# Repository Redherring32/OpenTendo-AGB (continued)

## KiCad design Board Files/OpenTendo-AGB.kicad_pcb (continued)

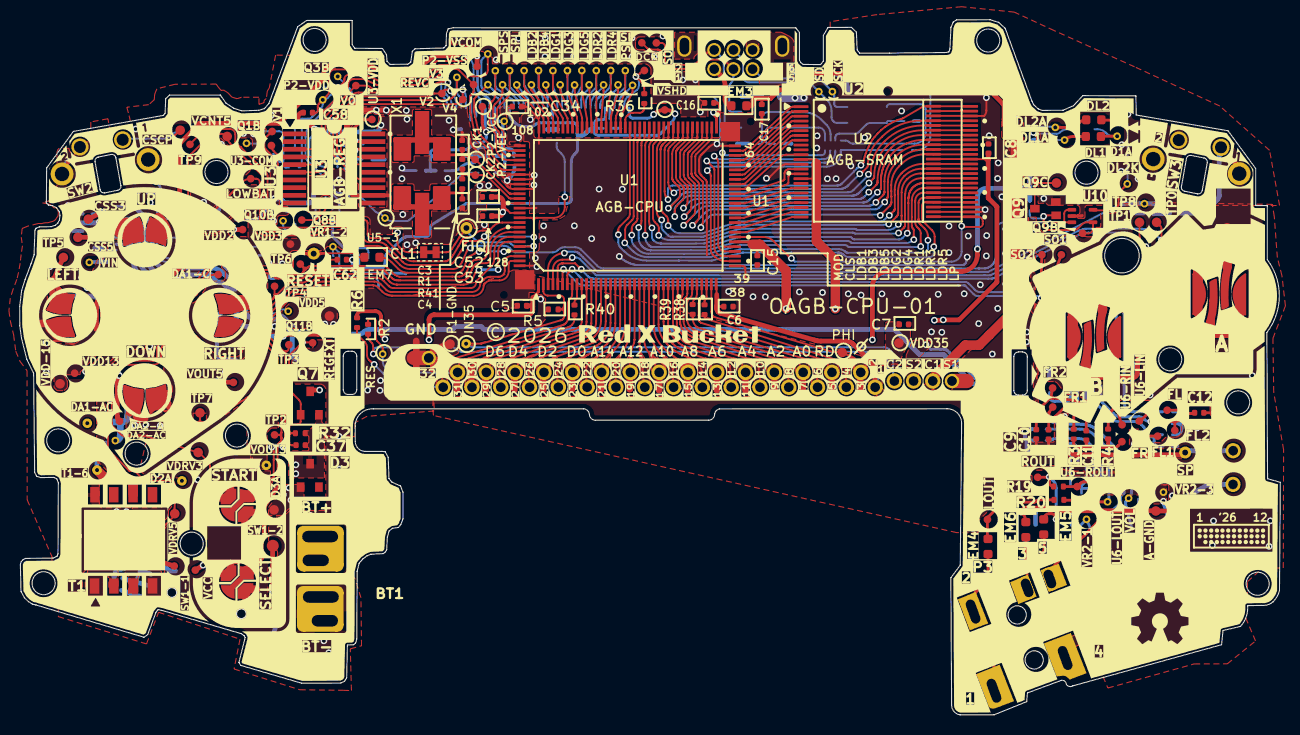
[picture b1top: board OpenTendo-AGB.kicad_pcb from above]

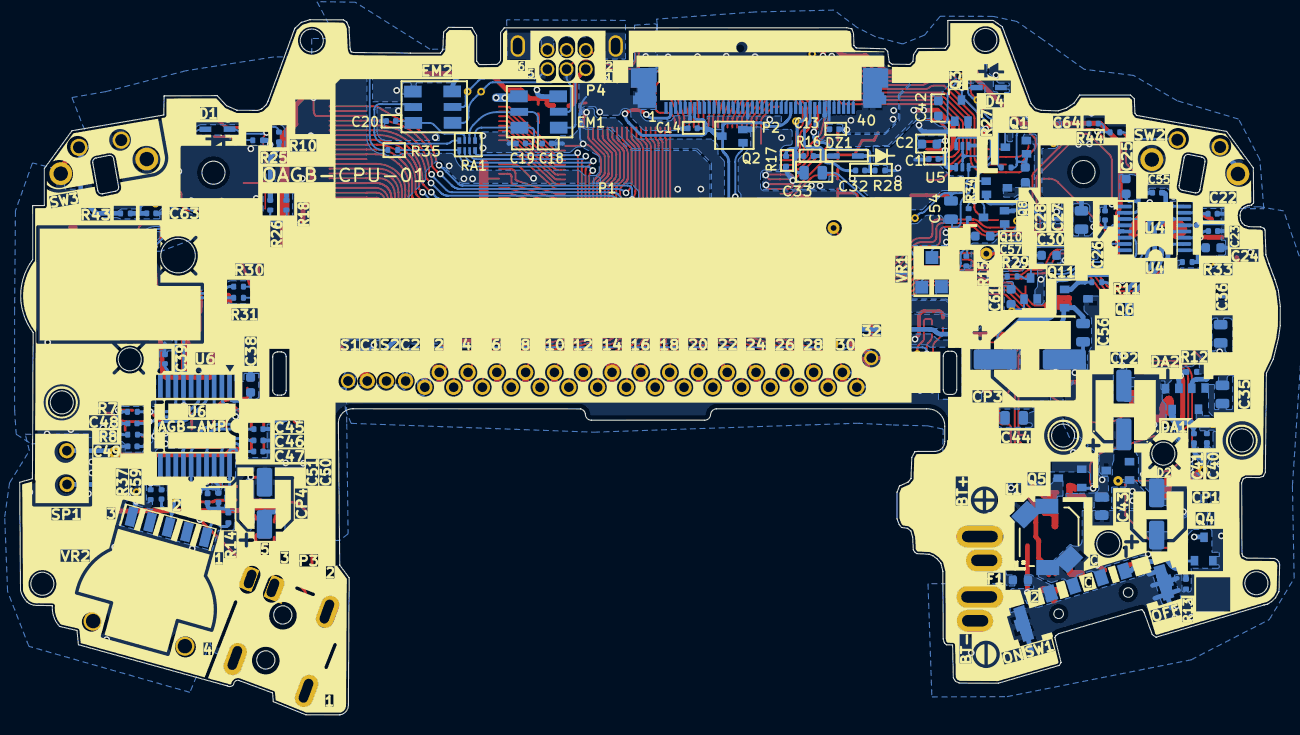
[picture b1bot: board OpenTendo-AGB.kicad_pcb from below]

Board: 2 copper layers, 131.3 x 72.4 mm, 273 parts (96 on the bottom side), 206 nets.

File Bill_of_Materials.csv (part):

Reference,Qty,Value,DNP,Exclude from BOM,Exclude from Board,Footprint,Datasheet
BT1,1,Battery,,,,OpenTendo-AGB:Battery,~
"C1,C37,C62,C63,C64",5,0.01u,,,,OpenTendo-AGB:C_0402_1005Metric,~
"C2,C24,C28,C30,C38,C42,C57,C61",8,1u,,,,OpenTendo-AGB:C_0603_1608Metric,~
C3,1,27p,,,,OpenTendo-AGB:C_0402_1005Metric,~
C4,1,33p,,,,OpenTendo-AGB:C_0402_1005Metric,~
"C5,C6,C7,C8,C13,C14,C15,C16,C17,C22,C23,C26,C32,C34,C39,C40,C41,C45,C46,C47,C50,C51,C52,C53,C55,C58,C59",27,0.1u,,,,OpenTendo-AGB:C_0402_1005Metric,~
"C9,C12",2,1000p,,,,OpenTendo-AGB:C_0402_1005Metric,~
"C10,C18,C19,C20,C49",5,100p,,,,OpenTendo-AGB:C_0402_1005Metric,~
"C11,C48",2,470p,,,,OpenTendo-AGB:C_0402_1005Metric,~
C25,1,0.47u,,,,OpenTendo-AGB:C_0603_1608Metric,~
"C27,C43,C54",3,4.7u,,,,OpenTendo-AGB:C_0805_2012Metric,~
"C33,C35,C36",3,1u,,,,OpenTendo-AGB:C_0805_2012Metric,~
"C44,C56",2,2.2u,,,,OpenTendo-AGB:C_0805_2012Metric,~
CL1,1,SolderJumper_2_Bridged,,Excluded from BOM,,OpenTendo-AGB:Jumper-Bridged,~
"CP1,CP4",2,100u,,,,OpenTendo-AGB:CP_Elec_5x5.3,~
CP2,1,100u,,,,OpenTendo-AGB:C_Elec_6.3x5.8,~
CP3,1,470u,,,,OpenTendo-AGB:C_Elec_8x10.2,~
D1,1,MA112,,,,OpenTendo-AGB:Diode,~
D2,1,RB411D,,,,OpenTendo-AGB:SOT-23,~
D3,1,RB491D,,,,OpenTendo-AGB:SOT-23,~
D4,1,ISS355,,,,OpenTendo-AGB:Diode,~
"DA1,DA2",2,DA204U,,,,OpenTendo-AGB:SOT-323,~
DL1,1,SML311UT,,,,OpenTendo-AGB:LED_0603_1608Metric,~
DL2,1,SML210MT,,,,OpenTendo-AGB:LED_0603_1608Metric,~
DZ1,1,RD4.7S,,,,OpenTendo-AGB:Diode,
"EM1,EM2",2,ACM4532-102-3P,,,,OpenTendo-AGB:EM,~
"EM3,EM7",2,HW601,,,,OpenTendo-AGB:L_0603_1608Metric,~
"EM4,EM5,EM6",3,BLM11B252SD,,,,OpenTendo-AGB:L_0603_1608Metric,~
F1,1,4341.25,,,,OpenTendo-AGB:Fuse_0603_1608Metric,~
L1,1,100u,,,,OpenTendo-AGB:Inductor,~
P1,1,CART,,,,OpenTendo-AGB:CartSlot,
P2,1,LCD,,,,OpenTendo-AGB:LCD-Connector,
P3,1,PHONE JACK,,,,OpenTendo-AGB:Audio-Jack,
P4,1,AGB-LINK,,,,OpenTendo-AGB:EXT,
Q1,1,DTA123J,,,,OpenTendo-AGB:SOT-323,
Q2,1,DTA114T,,,,OpenTendo-AGB:SOT-323,
"Q3,Q10",2,DTC114Y,,,,OpenTendo-AGB:SOT-323,
"Q4,Q5",2,FDV303N,,,,OpenTendo-AGB:SOT-23,~
Q6,1,2SK1582,,,,OpenTendo-AGB:SOT-23,~
Q7,1,SSM3J01F,,,,OpenTendo-AGB:SOT-23,~
"Q8,Q9",2,2SC4081,,,,OpenTendo-AGB:SOT-323,~
Q11,1,DTA114Y,,,,OpenTendo-AGB:SOT-323,
R1,1,1.5M,,,,OpenTendo-AGB:R_0402_1005Metric,~
R2,1,10k,,,,OpenTendo-AGB:R_0402_1005Metric,~
"R3,R4,R7,R8,R30,R31",6,47k,,,,OpenTendo-AGB:R_0402_1005Metric,~
"R5,R6,R17,R35",4,100k,,,,OpenTendo-AGB:R_0402_1005Metric,~
"R10,R37",2,470,,,,OpenTendo-AGB:R_0402_1005Metric,~
"R11,R12,R13",3,150,,,,OpenTendo-AGB:R_0402_1005Metric,~
R14,1,4.7k,,,,OpenTendo-AGB:R_0402_1005Metric,~
"R15,R16,R18",3,33k,,,,OpenTendo-AGB:R_0402_1005Metric,~
"R19,R20,R40,R43,R44",5,15,,,,OpenTendo-AGB:R_0402_1005Metric,~
"R25,R38,R39",3,47,,,,OpenTendo-AGB:R_0402_1005Metric,~
"R26,R34",2,15k,,,,OpenTendo-AGB:R_0402_1005Metric,~
R27,1,200k,,,,OpenTendo-AGB:R_0402_1005Metric,~
R28,1,56k,,,,OpenTendo-AGB:R_0402_1005Metric,~
R29,1,18k,,,,OpenTendo-AGB:R_0402_1005Metric,~
R32,1,1M,,,,OpenTendo-AGB:R_0402_1005Metric,~
R33,1,5.1,,,,OpenTendo-AGB:R_0402_1005Metric,~
R36,1,270,,,,OpenTendo-AGB:R_0402_1005Metric,~
R41,1,2.2k,,,,OpenTendo-AGB:R_0402_1005Metric,~
RA1,1,330,,,,OpenTendo-AGB:RA,
SP1,1,Speaker,,,,OpenTendo-AGB:Speaker,~
SW1,1,AGB-SW,,,,OpenTendo-AGB:Power Switch,
SW2,1,SW_Push,,,,OpenTendo-AGB:L,~
SW3,1,SW_Push,,,,OpenTendo-AGB:R,~
SW4,1,AGB-A-B,,,,OpenTendo-AGB:AB,~
SW5,1,AGB-ST-SEL,,,,OpenTendo-AGB:StartSelect,
SW6,1,AGB-DPAD,,,,OpenTendo-AGB:DPAD,
T1,1,AGB-XFRM,,,,OpenTendo-AGB:Coil,
TP0,1,TP0,,,,OpenTendo-AGB:TestPoint_Pad_D1.0mm,
TP1,1,TP1,,,,OpenTendo-AGB:TestPoint_Pad_D1.0mm,
TP2,1,TP2,,,,OpenTendo-AGB:TestPoint_Pad_D0.8mm,
TP3,1,TP3,,,,OpenTendo-AGB:TestPoint_Pad_D0.8mm,
TP4,1,TP4,,,,OpenTendo-AGB:TestPoint_Pad_D0.8mm,
TP5,1,TP5,,,,OpenTendo-AGB:TestPoint_Pad_D1.0mm,
TP6,1,TP6,,,,OpenTendo-AGB:TestPoint_Pad_D0.8mm,
TP7,1,TP7,,,,OpenTendo-AGB:TestPoint_Pad_D1.0mm,
TP8,1,TP8,,,,OpenTendo-AGB:TestPoint_Pad_D0.8mm_VIA,
TP9,1,TP9,,,,OpenTendo-AGB:TestPoint_Pad_D0.8mm,
TP10,1,VOUT3,,,,OpenTendo-AGB:TestPoint_Pad_D1.0mm_VIA,
TP11,1,VDRV3,,,,OpenTendo-AGB:TestPoint_Pad_D1.0mm,
TP12,1,VDD2,,,,OpenTendo-AGB:TestPoint_Pad_D0.8mm,
TP13,1,VDRV5,,,,OpenTendo-AGB:TestPoint_Pad_D1.0mm,
TP14,1,VOUT5,,,,OpenTendo-AGB:TestPoint_Pad_D0.8mm,
TP15,1,~{RESET},,,,OpenTendo-AGB:TestPoint_Pad_D1.25mm_VIA,
TP16,1,D3A,,,,OpenTendo-AGB:TestPoint_Pad_D1.0mm,
TP17,1,D2A,,,,OpenTendo-AGB:TestPoint_Pad_D1.0mm_VIA,
TP18,1,DA2-AC,,,,OpenTendo-AGB:TestPoint_Pad_D0.8mm_VIA,
TP19,1,DA1-AC,,,,OpenTendo-AGB:TestPoint_Pad_D1.0mm_VIA,
TP20,1,DA2-A,,,,OpenTendo-AGB:TestPoint_Pad_D0.8mm,
TP21,1,DA1-C,,,,OpenTendo-AGB:TestPoint_Pad_D0.8mm,
TP22,1,VDD13,,,,OpenTendo-AGB:TestPoint_Pad_D0.8mm,
TP23,1,VDD-15,,,,OpenTendo-AGB:TestPoint_Pad_D1.0mm,
TP24,1,VDD5,,,,OpenTendo-AGB:TestPoint_Pad_D1.0mm,
TP25,1,Q8B,,,,OpenTendo-AGB:TestPoint_Pad_D0.8mm,
TP26,1,VSHD,,,,OpenTendo-AGB:TestPoint_Pad_D0.8mm,
TP27,1,Q10B,,,,OpenTendo-AGB:TestPoint_Pad_D0.8mm_VIA,
TP28,1,LOWBAT,,,,OpenTendo-AGB:TestPoint_Pad_D0.8mm,
TP29,1,DL2A,,,,OpenTendo-AGB:TestPoint_Pad_D0.8mm_VIA,
TP30,1,DL2K,,,,OpenTendo-AGB:TestPoint_Pad_D0.8mm_VIA,
TP31,1,DL1A,,,,OpenTendo-AGB:TestPoint_Pad_D0.8mm_VIA,
TP32,1,D1A,,,,OpenTendo-AGB:TestPoint_Pad_D0.8mm_VIA,
TP33,1,Q9C,,,,OpenTendo-AGB:TestPoint_Pad_D1.0mm,
TP34,1,Q9B,,,,OpenTendo-AGB:TestPoint_Pad_D0.8mm,
TP35,1,Q11B,,,,OpenTendo-AGB:TestPoint_Pad_D0.8mm_VIA,
TP36,1,MOD,,,,OpenTendo-AGB:TestPoint_Pad_D0.8mm_VIA,
TP37,1,SPS,,,,OpenTendo-AGB:TestPoint_Pad_D0.8mm_VIA,
TP38,1,CLS,,,,OpenTendo-AGB:TestPoint_Pad_D0.8mm_VIA,
TP39,1,SPL,,,,OpenTendo-AGB:TestPoint_Pad_D0.8mm_VIA,
TP40,1,LDB1,,,,OpenTendo-AGB:TestPoint_Pad_D0.8mm_VIA,
TP41,1,LDB2,,,,OpenTendo-AGB:TestPoint_Pad_D0.8mm_VIA,
TP42,1,LDB3,,,,OpenTendo-AGB:TestPoint_Pad_D0.8mm_VIA,
TP43,1,LDB4,,,,OpenTendo-AGB:TestPoint_Pad_D0.8mm_VIA,
TP44,1,LDB5,,,,OpenTendo-AGB:TestPoint_Pad_D0.8mm_VIA,
TP45,1,LDG1,,,,OpenTendo-AGB:TestPoint_Pad_D0.8mm_VIA,
TP46,1,LDG2,,,,OpenTendo-AGB:TestPoint_Pad_D0.8mm_VIA,
TP47,1,LDG3,,,,OpenTendo-AGB:TestPoint_Pad_D0.8mm_VIA,
TP48,1,LDG4,,,,OpenTendo-AGB:TestPoint_Pad_D0.8mm_VIA,
TP49,1,LDG5,,,,OpenTendo-AGB:TestPoint_Pad_D0.8mm_VIA,
TP50,1,LDR1,,,,OpenTendo-AGB:TestPoint_Pad_D0.8mm_VIA,
TP51,1,LDR2,,,,OpenTendo-AGB:TestPoint_Pad_D0.8mm_VIA,
TP52,1,LDR3,,,,OpenTendo-AGB:TestPoint_Pad_D0.8mm_VIA,
TP53,1,LDR4,,,,OpenTendo-AGB:TestPoint_Pad_D0.8mm_VIA,
TP54,1,LDR5,,,,OpenTendo-AGB:TestPoint_Pad_D0.8mm_VIA,
TP55,1,PS,,,,OpenTendo-AGB:TestPoint_Pad_D0.8mm_VIA,
TP56,1,LP,,,,OpenTendo-AGB:TestPoint_Pad_D0.8mm_VIA,
TP57,1,DCK,,,,OpenTendo-AGB:TestPoint_Pad_D0.8mm,
TP58,1,P2-VSS,,,,OpenTendo-AGB:TestPoint_Pad_D0.8mm,
TP59,1,P2-VCC,,,,OpenTendo-AGB:TestPoint_Pad_D0.8mm,
TP60,1,P2-VDD,,,,OpenTendo-AGB:TestPoint_Pad_D0.8mm_VIA,
TP61,1,P2-VEE,,,,OpenTendo-AGB:TestPoint_Pad_D0.8mm_VIA,
TP62,1,REVC,,,,OpenTendo-AGB:TestPoint_Pad_D0.8mm,
TP63,1,U3-VDD,,,,OpenTendo-AGB:TestPoint_Pad_D0.8mm,
TP64,1,V0,,,,OpenTendo-AGB:TestPoint_Pad_D0.8mm,
TP65,1,V1,,,,OpenTendo-AGB:TestPoint_Pad_D0.8mm,
TP66,1,V2,,,,OpenTendo-AGB:TestPoint_Pad_D0.8mm,
TP67,1,V3,,,,OpenTendo-AGB:TestPoint_Pad_D0.8mm_VIA,
TP68,1,V4,,,,OpenTendo-AGB:TestPoint_Pad_D0.8mm,
TP69,1,U3-COM,,,,OpenTendo-AGB:TestPoint_Pad_D0.8mm,
TP70,1,VCOM,,,,OpenTendo-AGB:TestPoint_Pad_D0.8mm_VIA,
TP71,1,VR1-2,,,,OpenTendo-AGB:TestPoint_Pad_D0.8mm_VIA,
TP72,1,U5-3,,,,OpenTendo-AGB:TestPoint_Pad_D0.8mm_VIA,
TP73,1,Q3B,,,,OpenTendo-AGB:TestPoint_Pad_D0.8mm_VIA,
TP74,1,Q1B,,,,OpenTendo-AGB:TestPoint_Pad_D0.8mm_VIA,
TP75,1,IN35,,,,OpenTendo-AGB:TestPoint_Pad_D1.0mm_VIA,
TP76,1,VDD35,,,,OpenTendo-AGB:TestPoint_Pad_D1.0mm,
TP77,1,PHI,,,,OpenTendo-AGB:TestPoint_Pad_D1.0mm,
TP78,1,RES,,,,OpenTendo-AGB:TestPoint_Pad_D0.8mm_VIA,
TP79,1,P1-GND,,,,OpenTendo-AGB:TestPoint_Pad_D1.0mm,
TP80,1,CK1,,,,OpenTendo-AGB:TestPoint_Pad_D0.8mm,
TP81,1,CK2,,,,OpenTendo-AGB:TestPoint_Pad_D0.8mm,
TP82,1,FIQ,,,,OpenTendo-AGB:TestPoint_Pad_D1.25mm_VIA,
TP83,1,SW1-2,,,,OpenTendo-AGB:TestPoint_Pad_D1.25mm,
TP84,1,SW1-1,,,,OpenTendo-AGB:TestPoint_Pad_D0.8mm,
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
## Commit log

2023-01-30 + Add Kicad project files
2025-12-31 Add .kicad_pcb file without images
